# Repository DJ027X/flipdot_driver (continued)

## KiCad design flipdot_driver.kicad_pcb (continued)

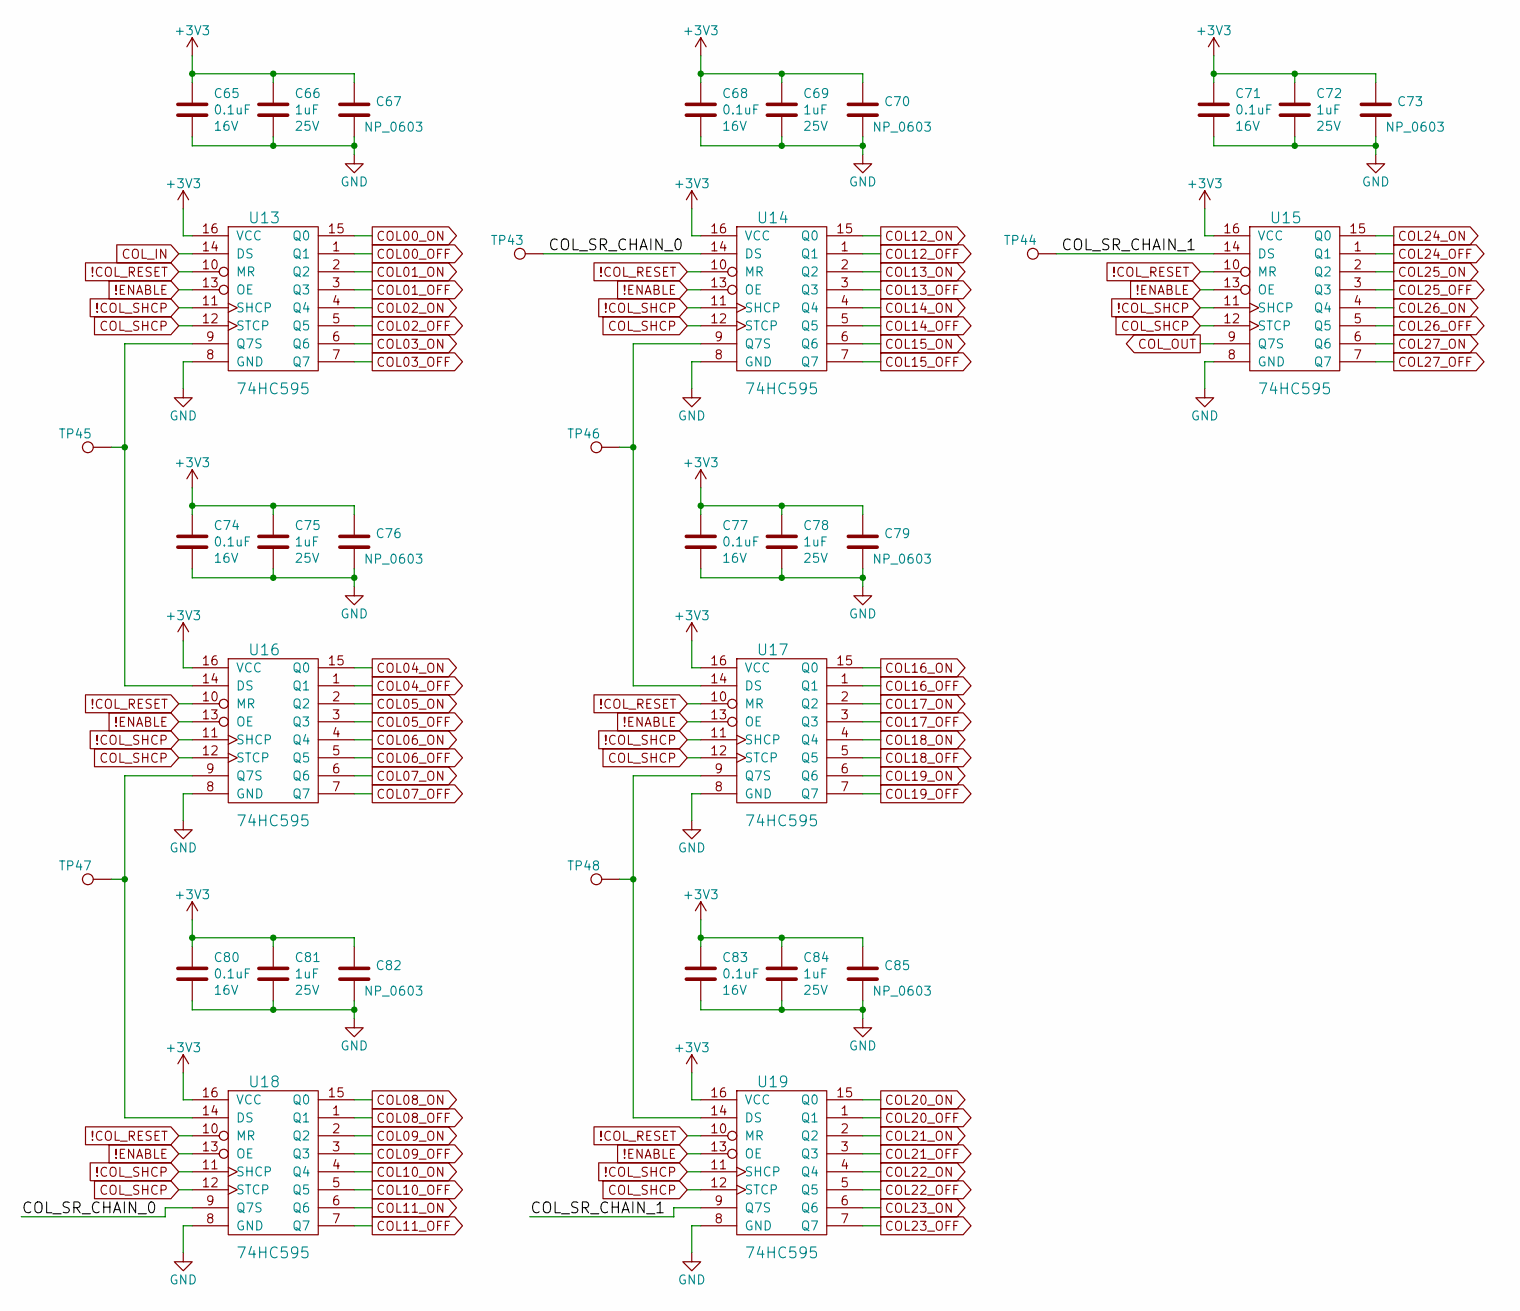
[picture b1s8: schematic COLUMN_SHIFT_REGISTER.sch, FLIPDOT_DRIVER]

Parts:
C65, C68, C71, C74, C77, C80, C83: CL10B104KO8NNNC; C_0603_1608Metric; Rating 16V
C66, C69, C72, C75, C78, C81, C84: CL10B105KA8NNNC; C_0603_1608Metric; Rating 25V
C67, C70, C73, C76, C79, C82, C85: NP_0603; C_0603_1608Metric
TP43, TP44, TP45, TP46, TP47, TP48: TestPoint; TestPoint_THTPad_D1.0mm_Drill0.5mm
U13, U14, U15, U16, U17, U18, U19: 74HC595; SOIC-16_3.9x9.9mm_P1.27mm

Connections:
!COL_RESET: U13.10 (MR), U14.10 (MR), U15.10 (MR), U16.10 (MR), U17.10 (MR), U18.10 (MR), U19.10 (MR); also elsewhere on the board
!COL_SHCP: U13.11 (SHCP), U14.11 (SHCP), U15.11 (SHCP), U16.11 (SHCP), U17.11 (SHCP), U18.11 (SHCP), U19.11 (SHCP); also elsewhere on the board
!ENABLE: U13.13 (OE), U14.13 (OE), U15.13 (OE), U16.13 (OE), U17.13 (OE), U18.13 (OE), U19.13 (OE); also elsewhere on the board
+3V3: C65.1, C66.1, C67.1, C68.1, C69.1, C70.1, C71.1, C72.1, C73.1, C74.1, C75.1, C76.1, C77.1, C78.1, C79.1, C80.1, C81.1, C82.1, C83.1, C84.1, C85.1, U13.16 (VCC), U14.16 (VCC), U15.16 (VCC), U16.16 (VCC), U17.16 (VCC), U18.16 (VCC), U19.16 (VCC); also elsewhere on the board
/COLUMN_SHIFT_REGISTER/COL_SR_CHAIN_0: TP43.1, U14.14 (DS), U18.9 (Q7S)
/COLUMN_SHIFT_REGISTER/COL_SR_CHAIN_1: TP44.1, U15.14 (DS), U19.9 (Q7S)
COL00_OFF: U13.1 (Q1); also elsewhere on the board
COL00_ON: U13.15 (Q0); also elsewhere on the board
COL01_OFF: U13.3 (Q3); also elsewhere on the board
COL01_ON: U13.2 (Q2); also elsewhere on the board
COL02_OFF: U13.5 (Q5); also elsewhere on the board
COL02_ON: U13.4 (Q4); also elsewhere on the board
COL03_OFF: U13.7 (Q7); also elsewhere on the board
COL03_ON: U13.6 (Q6); also elsewhere on the board
COL04_OFF: U16.1 (Q1); also elsewhere on the board
COL04_ON: U16.15 (Q0); also elsewhere on the board
COL05_OFF: U16.3 (Q3); also elsewhere on the board
COL05_ON: U16.2 (Q2); also elsewhere on the board
COL06_OFF: U16.5 (Q5); also elsewhere on the board
COL06_ON: U16.4 (Q4); also elsewhere on the board
COL07_OFF: U16.7 (Q7); also elsewhere on the board
COL07_ON: U16.6 (Q6); also elsewhere on the board
COL08_OFF: U18.1 (Q1); also elsewhere on the board
COL08_ON: U18.15 (Q0); also elsewhere on the board
COL09_OFF: U18.3 (Q3); also elsewhere on the board
COL09_ON: U18.2 (Q2); also elsewhere on the board
COL10_OFF: U18.5 (Q5); also elsewhere on the board
COL10_ON: U18.4 (Q4); also elsewhere on the board
COL11_OFF: U18.7 (Q7); also elsewhere on the board
COL11_ON: U18.6 (Q6); also elsewhere on the board
COL12_OFF: U14.1 (Q1); also elsewhere on the board
COL12_ON: U14.15 (Q0); also elsewhere on the board
COL13_OFF: U14.3 (Q3); also elsewhere on the board
COL13_ON: U14.2 (Q2); also elsewhere on the board
COL14_OFF: U14.5 (Q5); also elsewhere on the board
COL14_ON: U14.4 (Q4); also elsewhere on the board
COL15_OFF: U14.7 (Q7); also elsewhere on the board
COL15_ON: U14.6 (Q6); also elsewhere on the board
COL16_OFF: U17.1 (Q1); also elsewhere on the board
COL16_ON: U17.15 (Q0); also elsewhere on the board
COL17_OFF: U17.3 (Q3); also elsewhere on the board
COL17_ON: U17.2 (Q2); also elsewhere on the board
COL18_OFF: U17.5 (Q5); also elsewhere on the board
COL18_ON: U17.4 (Q4); also elsewhere on the board
COL19_OFF: U17.7 (Q7); also elsewhere on the board
COL19_ON: U17.6 (Q6); also elsewhere on the board
COL20_OFF: U19.1 (Q1); also elsewhere on the board
COL20_ON: U19.15 (Q0); also elsewhere on the board
COL21_OFF: U19.3 (Q3); also elsewhere on the board
COL21_ON: U19.2 (Q2); also elsewhere on the board
COL22_OFF: U19.5 (Q5); also elsewhere on the board
COL22_ON: U19.4 (Q4); also elsewhere on the board
COL23_OFF: U19.7 (Q7); also elsewhere on the board
COL23_ON: U19.6 (Q6); also elsewhere on the board
COL24_OFF: U15.1 (Q1); also elsewhere on the board
COL24_ON: U15.15 (Q0); also elsewhere on the board
COL25_OFF: U15.3 (Q3); also elsewhere on the board
COL25_ON: U15.2 (Q2); also elsewhere on the board
COL26_OFF: U15.5 (Q5); also elsewhere on the board
COL26_ON: U15.4 (Q4); also elsewhere on the board
COL27_OFF: U15.7 (Q7); also elsewhere on the board
COL27_ON: U15.6 (Q6); also elsewhere on the board
COL_IN: U13.14 (DS); also elsewhere on the board
COL_OUT: U15.9 (Q7S); also elsewhere on the board
COL_SHCP: U13.12 (STCP), U14.12 (STCP), U15.12 (STCP), U16.12 (STCP), U17.12 (STCP), U18.12 (STCP), U19.12 (STCP); also elsewhere on the board
GND: C65.2, C66.2, C67.2, C68.2, C69.2, C70.2, C71.2, C72.2, C73.2, C74.2, C75.2, C76.2, C77.2, C78.2, C79.2, C80.2, C81.2, C82.2, C83.2, C84.2, C85.2, U13.8 (GND), U14.8 (GND), U15.8 (GND), U16.8 (GND), U17.8 (GND), U18.8 (GND), U19.8 (GND); also elsewhere on the board
unnamed: TP45.1, U13.9 (Q7S), U16.14 (DS)
unnamed: TP46.1, U14.9 (Q7S), U17.14 (DS)
unnamed: TP47.1, U16.9 (Q7S), U18.14 (DS)
unnamed: TP48.1, U17.9 (Q7S), U19.14 (DS)

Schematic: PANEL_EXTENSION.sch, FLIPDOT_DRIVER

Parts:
C86, C87: CL10B104KO8NNNC; C_0603_1608Metric; Rating 16V
J10: Conn_01x08_Male; PinHeader_1x08_P2.54mm_Horizontal
R89, R90, R91, R92: CRG0603F4K7; R_0603_1608Metric; TOLERANCE 5%
TP49, TP50, TP51, TP52, TP53, TP54, TP55, TP56, TP57, TP58, TP59, TP60: TestPoint; TestPoint_THTPad_D1.0mm_Drill0.5mm
U20, U22: SGM3157YC6; SOT-363_SC-70-6
U21, U23: CM1293A-04SO; SOT-457

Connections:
!COL_RESET: J10.3, TP58.1, U23.3 (CH2); also elsewhere on the board
!ENABLE: J10.2, TP59.1, U23.4 (CH3); also elsewhere on the board
+3V3: C86.1, C87.1, U20.5 (VCC), U21.5 (V+), U22.5 (VCC), U23.5 (V+); also elsewhere on the board
/PANEL_EXTENSION/COL_DATA: J10.5, R91.1, TP56.1, U21.6 (CH4), U22.4 (COM)
/PANEL_EXTENSION/ROW_DATA: J10.8, R89.1, TP53.1, U20.4 (COM), U21.1 (CH1)
COL_IN: TP52.1, U22.3 (N_OP); also elsewhere on the board
COL_MODE_SEL: R92.1, U22.6 (IN); also elsewhere on the board
COL_OUT: TP51.1, U22.1 (N_CL); also elsewhere on the board
COL_SHCP: J10.4, TP57.1, U23.1 (CH1); also elsewhere on the board
GND: C86.2, C87.2, J10.1, R89.2, R90.2, R91.2, R92.2, TP60.1, U20.2 (GND), U21.2 (V-), U22.2 (GND), U23.2 (V-), U23.6 (CH4); also elsewhere on the board
ROW_IN: TP50.1, U20.3 (N_OP); also elsewhere on the board
ROW_MODE_SEL: R90.1, U20.6 (IN); also elsewhere on the board
ROW_ON: J10.6, TP55.1, U21.4 (CH3); also elsewhere on the board
ROW_OUT: TP49.1, U20.1 (N_CL); also elsewhere on the board
ROW_SHCP: J10.7, TP54.1, U21.3 (CH2); also elsewhere on the board

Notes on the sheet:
CONN_GND

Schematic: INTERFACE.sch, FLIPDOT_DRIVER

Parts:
J11: 3x32_1&3_loaded_2.5mm_0.1in_female_header; 32x3_POP_1_3
Q15: DMG6602; TSOT-23-6
R93: CRG0603F4K7; R_0603_1608Metric; TOLERANCE 5%
TP61, TP62: TestPoint; TestPoint_THTPad_D1.0mm_Drill0.5mm

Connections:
+24V: J11.3, J11.4; also elsewhere on the board
COL00: J11.37; also elsewhere on the board
COL01: J11.38; also elsewhere on the board
COL02: J11.39; also elsewhere on the board
COL03: J11.40; also elsewhere on the board
COL04: J11.41; also elsewhere on the board
COL05: J11.42; also elsewhere on the board
COL06: J11.43; also elsewhere on the board
COL07: J11.44; also elsewhere on the board
COL08: J11.45; also elsewhere on the board
COL09: J11.46; also elsewhere on the board
COL10: J11.47; also elsewhere on the board
COL11: J11.48; also elsewhere on the board
COL12: J11.49; also elsewhere on the board
COL13: J11.50; also elsewhere on the board
COL14: J11.51; also elsewhere on the board
COL15: J11.52; also elsewhere on the board
COL16: J11.53; also elsewhere on the board
COL17: J11.54; also elsewhere on the board
COL18: J11.55; also elsewhere on the board
COL19: J11.56; also elsewhere on the board
COL20: J11.57; also elsewhere on the board
COL21: J11.58; also elsewhere on the board
COL22: J11.59; also elsewhere on the board
COL23: J11.60; also elsewhere on the board
COL24: J11.61; also elsewhere on the board
COL25: J11.62; also elsewhere on the board
COL26: J11.63; also elsewhere on the board
COL27: J11.64; also elsewhere on the board
GND: Q15.5 (S), R93.2; also elsewhere on the board
LED_PWM: Q15.1 (G), R93.1, TP62.1; also elsewhere on the board
unnamed: J11.1, J11.2, Q15.6 (D), TP61.1
ROW00N: J11.36; also elsewhere on the board
ROW00P: J11.35; also elsewhere on the board
ROW01N: J11.6; also elsewhere on the board
ROW01P: J11.5; also elsewhere on the board
ROW02N: J11.34; also elsewhere on the board
ROW02P: J11.33; also elsewhere on the board
ROW03N: J11.8; also elsewhere on the board
ROW03P: J11.7; also elsewhere on the board
ROW04N: J11.32; also elsewhere on the board
ROW04P: J11.31; also elsewhere on the board
ROW05N: J11.10; also elsewhere on the board
ROW05P: J11.9; also elsewhere on the board
ROW06N: J11.30; also elsewhere on the board
ROW06P: J11.29; also elsewhere on the board
ROW07N: J11.12; also elsewhere on the board
ROW07P: J11.11; also elsewhere on the board
ROW08N: J11.28; also elsewhere on the board
ROW08P: J11.27; also elsewhere on the board
ROW09N: J11.14; also elsewhere on the board
ROW09P: J11.13; also elsewhere on the board
ROW10N: J11.26; also elsewhere on the board
ROW10P: J11.25; also elsewhere on the board
ROW11N: J11.16; also elsewhere on the board
ROW11P: J11.15; also elsewhere on the board
ROW12N: J11.24; also elsewhere on the board
ROW12P: J11.23; also elsewhere on the board
ROW13N: J11.18; also elsewhere on the board
ROW13P: J11.17; also elsewhere on the board
ROW14N: J11.22; also elsewhere on the board
ROW14P: J11.21; also elsewhere on the board
ROW15N: J11.20; also elsewhere on the board
ROW15P: J11.19; also elsewhere on the board

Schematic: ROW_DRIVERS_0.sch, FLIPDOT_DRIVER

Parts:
D18, D19, D20, D21, D22, D23, D24, D25: MMBZ5243BLT1G; SOT-23; Rating 13V
Q16, Q17, Q20, Q21: DMG6602; TSOT-23-6
Q18, Q19, Q22, Q23: SSM3K35AMFV; SOT-723
R94, R95, R96, R97, R98, R99, R100, R101, R102, R103, R104, R105: CRG0603F4K7; R_0603_1608Metric; TOLERANCE 5%
TP63, TP64, TP66, TP68, TP70, TP72, TP74: TestPoint; TestPoint_THTPad_D1.0mm_Drill0.5mm

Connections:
+12V: D18.1 (K), D19.1 (K), D22.1 (K), D23.1 (K), Q16.2 (S), Q17.2 (S), Q20.2 (S), Q21.2 (S), R94.1, R95.1, R100.1, R101.1, TP63.1; also elsewhere on the board
GND: D20.2 (A), D21.2 (A), D24.2 (A), D25.2 (A), Q16.5 (S), Q17.5 (S), Q18.2 (S), Q19.2 (S), Q20.5 (S), Q21.5 (S), Q22.2 (S), Q23.2 (S), R96.2, R97.2, R98.2, R99.2, R102.2, R103.2, R104.2, R105.2, TP70.1; also elsewhere on the board
unnamed: Q16.3 (G), Q18.3 (D), R94.2, TP64.1
unnamed: Q17.3 (G), Q19.3 (D), R95.2
unnamed: Q20.3 (G), Q22.3 (D), R100.2
unnamed: Q21.3 (G), Q23.3 (D), R101.2
ROW00N: D20.1 (K), Q16.6 (D), TP72.1; also elsewhere on the board
ROW00P: D18.2 (A), Q16.4 (D), TP68.1; also elsewhere on the board
ROW00_OFF: Q16.1 (G), R98.1, TP74.1; also elsewhere on the board
ROW00_ON: Q18.1 (G), R96.1, TP66.1; also elsewhere on the board
ROW01N: D21.1 (K), Q17.6 (D); also elsewhere on the board
ROW01P: D19.2 (A), Q17.4 (D); also elsewhere on the board
ROW01_OFF: Q17.1 (G), R99.1; also elsewhere on the board
ROW01_ON: Q19.1 (G), R97.1; also elsewhere on the board
ROW02N: D24.1 (K), Q20.6 (D); also elsewhere on the board
ROW02P: D22.2 (A), Q20.4 (D); also elsewhere on the board
ROW02_OFF: Q20.1 (G), R104.1; also elsewhere on the board
ROW02_ON: Q22.1 (G), R102.1; also elsewhere on the board
ROW03N: D25.1 (K), Q21.6 (D); also elsewhere on the board
ROW03P: D23.2 (A), Q21.4 (D); also elsewhere on the board
ROW03_OFF: Q21.1 (G), R105.1; also elsewhere on the board
ROW03_ON: Q23.1 (G), R103.1; also elsewhere on the board

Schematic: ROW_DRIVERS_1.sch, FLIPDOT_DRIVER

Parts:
D26, D27, D28, D29, D30, D31, D32, D33: MMBZ5243BLT1G; SOT-23; Rating 13V
Q24, Q25, Q28, Q29: DMG6602; TSOT-23-6
Q26, Q27, Q30, Q31: SSM3K35AMFV; SOT-723
R106, R107, R108, R109, R110, R111, R112, R113, R114, R115, R116, R117: CRG0603F4K7; R_0603_1608Metric; TOLERANCE 5%

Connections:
+12V: D26.1 (K), D27.1 (K), D30.1 (K), D31.1 (K), Q24.2 (S), Q25.2 (S), Q28.2 (S), Q29.2 (S), R106.1, R107.1, R112.1, R113.1; also elsewhere on the board
GND: D28.2 (A), D29.2 (A), D32.2 (A), D33.2 (A), Q24.5 (S), Q25.5 (S), Q26.2 (S), Q27.2 (S), Q28.5 (S), Q29.5 (S), Q30.2 (S), Q31.2 (S), R108.2, R109.2, R110.2, R111.2, R114.2, R115.2, R116.2, R117.2; also elsewhere on the board
unnamed: Q24.3 (G), Q26.3 (D), R106.2
unnamed: Q25.3 (G), Q27.3 (D), R107.2
unnamed: Q28.3 (G), Q30.3 (D), R112.2
unnamed: Q29.3 (G), Q31.3 (D), R113.2
ROW04N: D28.1 (K), Q24.6 (D); also elsewhere on the board
ROW04P: D26.2 (A), Q24.4 (D); also elsewhere on the board
ROW04_OFF: Q24.1 (G), R110.1; also elsewhere on the board
ROW04_ON: Q26.1 (G), R108.1; also elsewhere on the board
ROW05N: D29.1 (K), Q25.6 (D); also elsewhere on the board
ROW05P: D27.2 (A), Q25.4 (D); also elsewhere on the board
ROW05_OFF: Q25.1 (G), R111.1; also elsewhere on the board
ROW05_ON: Q27.1 (G), R109.1; also elsewhere on the board
ROW06N: D32.1 (K), Q28.6 (D); also elsewhere on the board
ROW06P: D30.2 (A), Q28.4 (D); also elsewhere on the board
ROW06_OFF: Q28.1 (G), R116.1; also elsewhere on the board
ROW06_ON: Q30.1 (G), R114.1; also elsewhere on the board
ROW07N: D33.1 (K), Q29.6 (D); also elsewhere on the board
ROW07P: D31.2 (A), Q29.4 (D); also elsewhere on the board
ROW07_OFF: Q29.1 (G), R117.1; also elsewhere on the board
ROW07_ON: Q31.1 (G), R115.1; also elsewhere on the board

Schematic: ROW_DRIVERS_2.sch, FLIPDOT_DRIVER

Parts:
D34, D35, D36, D37, D38, D39, D40, D41: MMBZ5243BLT1G; SOT-23; Rating 13V
Q32, Q33, Q36, Q37: DMG6602; TSOT-23-6
Q34, Q35, Q38, Q39: SSM3K35AMFV; SOT-723
R118, R119, R120, R121, R122, R123, R124, R125, R126, R127, R128, R129: CRG0603F4K7; R_0603_1608Metric; TOLERANCE 5%

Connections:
+12V: D34.1 (K), D35.1 (K), D38.1 (K), D39.1 (K), Q32.2 (S), Q33.2 (S), Q36.2 (S), Q37.2 (S), R118.1, R119.1, R124.1, R125.1; also elsewhere on the board
GND: D36.2 (A), D37.2 (A), D40.2 (A), D41.2 (A), Q32.5 (S), Q33.5 (S), Q34.2 (S), Q35.2 (S), Q36.5 (S), Q37.5 (S), Q38.2 (S), Q39.2 (S), R120.2, R121.2, R122.2, R123.2, R126.2, R127.2, R128.2, R129.2; also elsewhere on the board
unnamed: Q32.3 (G), Q34.3 (D), R118.2
unnamed: Q33.3 (G), Q35.3 (D), R119.2
unnamed: Q36.3 (G), Q38.3 (D), R124.2
unnamed: Q37.3 (G), Q39.3 (D), R125.2
ROW08N: D36.1 (K), Q32.6 (D); also elsewhere on the board
ROW08P: D34.2 (A), Q32.4 (D); also elsewhere on the board
ROW08_OFF: Q32.1 (G), R122.1; also elsewhere on the board
ROW08_ON: Q34.1 (G), R120.1; also elsewhere on the board
ROW09N: D37.1 (K), Q33.6 (D); also elsewhere on the board
ROW09P: D35.2 (A), Q33.4 (D); also elsewhere on the board
ROW09_OFF: Q33.1 (G), R123.1; also elsewhere on the board
ROW09_ON: Q35.1 (G), R121.1; also elsewhere on the board
ROW10N: D40.1 (K), Q36.6 (D); also elsewhere on the board
ROW10P: D38.2 (A), Q36.4 (D); also elsewhere on the board
ROW10_OFF: Q36.1 (G), R128.1; also elsewhere on the board
ROW10_ON: Q38.1 (G), R126.1; also elsewhere on the board
ROW11N: D41.1 (K), Q37.6 (D); also elsewhere on the board
ROW11P: D39.2 (A), Q37.4 (D); also elsewhere on the board
ROW11_OFF: Q37.1 (G), R129.1; also elsewhere on the board
ROW11_ON: Q39.1 (G), R127.1; also elsewhere on the board

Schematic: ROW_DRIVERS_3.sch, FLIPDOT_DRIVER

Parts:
D42, D43, D44, D45, D46, D47, D48, D49: MMBZ5243BLT1G; SOT-23; Rating 13V
Q40, Q41, Q44, Q45: DMG6602; TSOT-23-6
Q42, Q43, Q46, Q47: SSM3K35AMFV; SOT-723
R130, R131, R132, R133, R134, R135, R136, R137, R138, R139, R140, R141: CRG0603F4K7; R_0603_1608Metric; TOLERANCE 5%

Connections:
+12V: D42.1 (K), D43.1 (K), D46.1 (K), D47.1 (K), Q40.2 (S), Q41.2 (S), Q44.2 (S), Q45.2 (S), R130.1, R131.1, R136.1, R137.1; also elsewhere on the board
GND: D44.2 (A), D45.2 (A), D48.2 (A), D49.2 (A), Q40.5 (S), Q41.5 (S), Q42.2 (S), Q43.2 (S), Q44.5 (S), Q45.5 (S), Q46.2 (S), Q47.2 (S), R132.2, R133.2, R134.2, R135.2, R138.2, R139.2, R140.2, R141.2; also elsewhere on the board
unnamed: Q40.3 (G), Q42.3 (D), R130.2
unnamed: Q41.3 (G), Q43.3 (D), R131.2
unnamed: Q44.3 (G), Q46.3 (D), R136.2
unnamed: Q45.3 (G), Q47.3 (D), R137.2
ROW12N: D44.1 (K), Q40.6 (D); also elsewhere on the board
ROW12P: D42.2 (A), Q40.4 (D); also elsewhere on the board
ROW12_OFF: Q40.1 (G), R134.1; also elsewhere on the board
ROW12_ON: Q42.1 (G), R132.1; also elsewhere on the board
ROW13N: D45.1 (K), Q41.6 (D); also elsewhere on the board
ROW13P: D43.2 (A), Q41.4 (D); also elsewhere on the board
ROW13_OFF: Q41.1 (G), R135.1; also elsewhere on the board
ROW13_ON: Q43.1 (G), R133.1; also elsewhere on the board
ROW14N: D48.1 (K), Q44.6 (D); also elsewhere on the board
ROW14P: D46.2 (A), Q44.4 (D); also elsewhere on the board
ROW14_OFF: Q44.1 (G), R140.1; also elsewhere on the board
ROW14_ON: Q46.1 (G), R138.1; also elsewhere on the board
ROW15N: D49.1 (K), Q45.6 (D); also elsewhere on the board
ROW15P: D47.2 (A), Q45.4 (D); also elsewhere on the board
ROW15_OFF: Q45.1 (G), R141.1; also elsewhere on the board
ROW15_ON: Q47.1 (G), R139.1; also elsewhere on the board

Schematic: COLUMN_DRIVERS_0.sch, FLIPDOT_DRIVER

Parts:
Q48, Q49, Q50, Q57, Q58, Q59: DMG6602; TSOT-23-6
Q51, Q52, Q53, Q54, Q55, Q56, Q60, Q61, Q62, Q63, Q64, Q65: SSM3K35AMFV; SOT-723
R142, R143, R144, R145, R146, R147, R148, R149, R150, R151, R152, R153, R154, R155, R156, R157, R158, R159, R160, R161, R162, R163, R164, R165: CRG0603F4K7; R_0603_1608Metric; TOLERANCE 5%
TP78, TP80, TP82, TP83, TP84, TP88, TP90: TestPoint; TestPoint_THTPad_D1.0mm_Drill0.5mm

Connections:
+12V: Q48.2 (S), Q49.2 (S), Q50.2 (S), Q57.2 (S), Q58.2 (S), Q59.2 (S), R142.1, R143.1, R144.1, R154.1, R155.1, R156.1, TP78.1; also elsewhere on the board
COL00: Q48.4 (D), Q48.6 (D), TP84.1; also elsewhere on the board
COL00_OFF: R145.2, R149.1, TP82.1; also elsewhere on the board
COL00_ON: Q51.1 (G), Q54.1 (G), R148.1, TP83.1; also elsewhere on the board
COL01: Q49.4 (D), Q49.6 (D); also elsewhere on the board
COL01_OFF: R146.2, R151.1; also elsewhere on the board
COL01_ON: Q52.1 (G), Q55.1 (G), R150.1; also elsewhere on the board
COL02: Q50.4 (D), Q50.6 (D); also elsewhere on the board
COL02_OFF: R147.2, R153.1; also elsewhere on the board
COL02_ON: Q53.1 (G), Q56.1 (G), R152.1; also elsewhere on the board
COL03: Q57.4 (D), Q57.6 (D); also elsewhere on the board
COL03_OFF: R157.2, R161.1; also elsewhere on the board
COL03_ON: Q60.1 (G), Q63.1 (G), R160.1; also elsewhere on the board
COL04: Q58.4 (D), Q58.6 (D); also elsewhere on the board
COL04_OFF: R158.2, R163.1; also elsewhere on the board
COL04_ON: Q61.1 (G), Q64.1 (G), R162.1; also elsewhere on the board
COL05: Q59.4 (D), Q59.6 (D); also elsewhere on the board
COL05_OFF: R159.2, R165.1; also elsewhere on the board
COL05_ON: Q62.1 (G), Q65.1 (G), R164.1; also elsewhere on the board
GND: Q48.5 (S), Q49.5 (S), Q50.5 (S), Q51.2 (S), Q52.2 (S), Q53.2 (S), Q54.2 (S), Q55.2 (S), Q56.2 (S), Q57.5 (S), Q58.5 (S), Q59.5 (S), Q60.2 (S), Q61.2 (S), Q62.2 (S), Q63.2 (S), Q64.2 (S), Q65.2 (S), R148.2, R149.2, R150.2, R151.2, R152.2, R153.2, R160.2, R161.2, R162.2, R163.2, R164.2, R165.2, TP90.1; also elsewhere on the board
unnamed: Q48.1 (G), Q54.3 (D), R145.1, TP88.1
unnamed: Q48.3 (G), Q51.3 (D), R142.2, TP80.1
unnamed: Q49.1 (G), Q55.3 (D), R146.1
unnamed: Q49.3 (G), Q52.3 (D), R143.2
unnamed: Q50.1 (G), Q56.3 (D), R147.1
unnamed: Q50.3 (G), Q53.3 (D), R144.2
unnamed: Q57.1 (G), Q63.3 (D), R157.1
unnamed: Q57.3 (G), Q60.3 (D), R154.2
unnamed: Q58.1 (G), Q64.3 (D), R158.1
unnamed: Q58.3 (G), Q61.3 (D), R155.2
unnamed: Q59.1 (G), Q65.3 (D), R159.1
unnamed: Q59.3 (G), Q62.3 (D), R156.2

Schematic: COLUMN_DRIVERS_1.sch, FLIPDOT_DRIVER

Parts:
Q66, Q67, Q68, Q75, Q76, Q77: DMG6602; TSOT-23-6
Q69, Q70, Q71, Q72, Q73, Q74, Q78, Q79, Q80, Q81, Q82, Q83: SSM3K35AMFV; SOT-723
R166, R167, R168, R169, R170, R171, R172, R173, R174, R175, R176, R177, R178, R179, R180, R181, R182, R183, R184, R185, R186, R187, R188, R189: CRG0603F4K7; R_0603_1608Metric; TOLERANCE 5%

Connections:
+12V: Q66.2 (S), Q67.2 (S), Q68.2 (S), Q75.2 (S), Q76.2 (S), Q77.2 (S), R166.1, R167.1, R168.1, R178.1, R179.1, R180.1; also elsewhere on the board
COL06: Q66.4 (D), Q66.6 (D); also elsewhere on the board
COL06_OFF: R169.2, R173.1; also elsewhere on the board
COL06_ON: Q69.1 (G), Q72.1 (G), R172.1; also elsewhere on the board
COL07: Q67.4 (D), Q67.6 (D); also elsewhere on the board
COL07_OFF: R170.2, R175.1; also elsewhere on the board
COL07_ON: Q70.1 (G), Q73.1 (G), R174.1; also elsewhere on the board
COL08: Q68.4 (D), Q68.6 (D); also elsewhere on the board
COL08_OFF: R171.2, R177.1; also elsewhere on the board
COL08_ON: Q71.1 (G), Q74.1 (G), R176.1; also elsewhere on the board
COL09: Q75.4 (D), Q75.6 (D); also elsewhere on the board
COL09_OFF: R181.2, R185.1; also elsewhere on the board
COL09_ON: Q78.1 (G), Q81.1 (G), R184.1; also elsewhere on the board
COL10: Q76.4 (D), Q76.6 (D); also elsewhere on the board
COL10_OFF: R182.2, R187.1; also elsewhere on the board
COL10_ON: Q79.1 (G), Q82.1 (G), R186.1; also elsewhere on the board
COL11: Q77.4 (D), Q77.6 (D); also elsewhere on the board
COL11_OFF: R183.2, R189.1; also elsewhere on the board
COL11_ON: Q80.1 (G), Q83.1 (G), R188.1; also elsewhere on the board
GND: Q66.5 (S), Q67.5 (S), Q68.5 (S), Q69.2 (S), Q70.2 (S), Q71.2 (S), Q72.2 (S), Q73.2 (S), Q74.2 (S), Q75.5 (S), Q76.5 (S), Q77.5 (S), Q78.2 (S), Q79.2 (S), Q80.2 (S), Q81.2 (S), Q82.2 (S), Q83.2 (S), R172.2, R173.2, R174.2, R175.2, R176.2, R177.2, R184.2, R185.2, R186.2, R187.2, R188.2, R189.2; also elsewhere on the board
unnamed: Q66.1 (G), Q72.3 (D), R169.1
unnamed: Q66.3 (G), Q69.3 (D), R166.2
unnamed: Q67.1 (G), Q73.3 (D), R170.1
unnamed: Q67.3 (G), Q70.3 (D), R167.2
unnamed: Q68.1 (G), Q74.3 (D), R171.1
unnamed: Q68.3 (G), Q71.3 (D), R168.2
unnamed: Q75.1 (G), Q81.3 (D), R181.1
unnamed: Q75.3 (G), Q78.3 (D), R178.2
unnamed: Q76.1 (G), Q82.3 (D), R182.1
unnamed: Q76.3 (G), Q79.3 (D), R179.2
unnamed: Q77.1 (G), Q83.3 (D), R183.1
unnamed: Q77.3 (G), Q80.3 (D), R180.2

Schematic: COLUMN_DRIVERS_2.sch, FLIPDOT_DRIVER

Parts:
Q84, Q85, Q86, Q93, Q94, Q95: DMG6602; TSOT-23-6
Q87, Q88, Q89, Q90, Q91, Q92, Q96, Q97, Q98, Q99, Q100, Q101: SSM3K35AMFV; SOT-723
R190, R191, R192, R193, R194, R195, R196, R197, R198, R199, R200, R201, R202, R203, R204, R205, R206, R207, R208, R209, R210, R211, R212, R213: CRG0603F4K7; R_0603_1608Metric; TOLERANCE 5%

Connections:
+12V: Q84.2 (S), Q85.2 (S), Q86.2 (S), Q93.2 (S), Q94.2 (S), Q95.2 (S), R190.1, R191.1, R192.1, R202.1, R203.1, R204.1; also elsewhere on the board
COL12: Q84.4 (D), Q84.6 (D); also elsewhere on the board
COL12_OFF: R193.2, R197.1; also elsewhere on the board
COL12_ON: Q87.1 (G), Q90.1 (G), R196.1; also elsewhere on the board
COL13: Q85.4 (D), Q85.6 (D); also elsewhere on the board
COL13_OFF: R194.2, R199.1; also elsewhere on the board
COL13_ON: Q88.1 (G), Q91.1 (G), R198.1; also elsewhere on the board
COL14: Q86.4 (D), Q86.6 (D); also elsewhere on the board
COL14_OFF: R195.2, R201.1; also elsewhere on the board
COL14_ON: Q89.1 (G), Q92.1 (G), R200.1; also elsewhere on the board
COL15: Q93.4 (D), Q93.6 (D); also elsewhere on the board
COL15_OFF: R205.2, R209.1; also elsewhere on the board
COL15_ON: Q96.1 (G), Q99.1 (G), R208.1; also elsewhere on the board
COL16: Q94.4 (D), Q94.6 (D); also elsewhere on the board
COL16_OFF: R206.2, R211.1; also elsewhere on the board
COL16_ON: Q97.1 (G), Q100.1 (G), R210.1; also elsewhere on the board
COL17: Q95.4 (D), Q95.6 (D); also elsewhere on the board
COL17_OFF: R207.2, R213.1; also elsewhere on the board
COL17_ON: Q98.1 (G), Q101.1 (G), R212.1; also elsewhere on the board
GND: Q84.5 (S), Q85.5 (S), Q86.5 (S), Q87.2 (S), Q88.2 (S), Q89.2 (S), Q90.2 (S), Q91.2 (S), Q92.2 (S), Q93.5 (S), Q94.5 (S), Q95.5 (S), Q96.2 (S), Q97.2 (S), Q98.2 (S), Q99.2 (S), Q100.2 (S), Q101.2 (S), R196.2, R197.2, R198.2, R199.2, R200.2, R201.2, R208.2, R209.2, R210.2, R211.2, R212.2, R213.2; also elsewhere on the board
unnamed: Q84.1 (G), Q90.3 (D), R193.1
unnamed: Q84.3 (G), Q87.3 (D), R190.2
unnamed: Q85.1 (G), Q91.3 (D), R194.1
unnamed: Q85.3 (G), Q88.3 (D), R191.2
unnamed: Q86.1 (G), Q92.3 (D), R195.1
unnamed: Q86.3 (G), Q89.3 (D), R192.2
unnamed: Q93.1 (G), Q99.3 (D), R205.1
unnamed: Q93.3 (G), Q96.3 (D), R202.2
unnamed: Q94.3 (G), Q97.3 (D), R203.2
unnamed: Q95.3 (G), Q98.3 (D), R204.2
unnamed: Q94.1 (G), Q100.3 (D), R206.1
unnamed: Q95.1 (G), Q101.3 (D), R207.1

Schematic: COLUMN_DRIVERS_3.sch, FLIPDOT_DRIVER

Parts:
Q102, Q103, Q104, Q111, Q112, Q113: DMG6602; TSOT-23-6
Q105, Q106, Q107, Q108, Q109, Q110, Q114, Q115, Q116, Q117, Q118, Q119: SSM3K35AMFV; SOT-723
R214, R215, R216, R217, R218, R219, R220, R221, R222, R223, R224, R225, R226, R227, R228, R229, R230, R231, R232, R233, R234, R235, R236, R237: CRG0603F4K7; R_0603_1608Metric; TOLERANCE 5%

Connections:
+12V: Q102.2 (S), Q103.2 (S), Q104.2 (S), Q111.2 (S), Q112.2 (S), Q113.2 (S), R214.1, R215.1, R216.1, R226.1, R227.1, R228.1; also elsewhere on the board
COL18: Q102.4 (D), Q102.6 (D); also elsewhere on the board
COL18_OFF: R217.2, R221.1; also elsewhere on the board
COL18_ON: Q105.1 (G), Q108.1 (G), R220.1; also elsewhere on the board
COL19: Q103.4 (D), Q103.6 (D); also elsewhere on the board
COL19_OFF: R218.2, R223.1; also elsewhere on the board
COL19_ON: Q106.1 (G), Q109.1 (G), R222.1; also elsewhere on the board
COL20: Q104.4 (D), Q104.6 (D); also elsewhere on the board
COL20_OFF: R219.2, R225.1; also elsewhere on the board
COL20_ON: Q107.1 (G), Q110.1 (G), R224.1; also elsewhere on the board
COL21: Q111.4 (D), Q111.6 (D); also elsewhere on the board
COL21_OFF: R229.2, R233.1; also elsewhere on the board
COL21_ON: Q114.1 (G), Q117.1 (G), R232.1; also elsewhere on the board
COL22: Q112.4 (D), Q112.6 (D); also elsewhere on the board
COL22_OFF: R230.2, R235.1; also elsewhere on the board
COL22_ON: Q115.1 (G), Q118.1 (G), R234.1; also elsewhere on the board
COL23: Q113.4 (D), Q113.6 (D); also elsewhere on the board
COL23_OFF: R231.2, R237.1; also elsewhere on the board
COL23_ON: Q116.1 (G), Q119.1 (G), R236.1; also elsewhere on the board
GND: Q102.5 (S), Q103.5 (S), Q104.5 (S), Q105.2 (S), Q106.2 (S), Q107.2 (S), Q108.2 (S), Q109.2 (S), Q110.2 (S), Q111.5 (S), Q112.5 (S), Q113.5 (S), Q114.2 (S), Q115.2 (S), Q116.2 (S), Q117.2 (S), Q118.2 (S), Q119.2 (S), R220.2, R221.2, R222.2, R223.2, R224.2, R225.2, R232.2, R233.2, R234.2, R235.2, R236.2, R237.2; also elsewhere on the board
unnamed: Q102.1 (G), Q108.3 (D), R217.1
unnamed: Q102.3 (G), Q105.3 (D), R214.2
unnamed: Q103.1 (G), Q109.3 (D), R218.1
unnamed: Q103.3 (G), Q106.3 (D), R215.2
unnamed: Q104.1 (G), Q110.3 (D), R219.1
unnamed: Q104.3 (G), Q107.3 (D), R216.2
unnamed: Q111.1 (G), Q117.3 (D), R229.1
unnamed: Q111.3 (G), Q114.3 (D), R226.2
unnamed: Q112.1 (G), Q118.3 (D), R230.1
unnamed: Q112.3 (G), Q115.3 (D), R227.2
unnamed: Q113.1 (G), Q119.3 (D), R231.1
unnamed: Q113.3 (G), Q116.3 (D), R228.2

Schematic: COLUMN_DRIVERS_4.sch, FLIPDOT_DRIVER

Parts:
Q120, Q121, Q122, Q129: DMG6602; TSOT-23-6
Q123, Q124, Q125, Q126, Q127, Q128, Q130, Q131: SSM3K35AMFV; SOT-723
R238, R239, R240, R241, R242, R243, R244, R245, R246, R247, R248, R249, R250, R251, R252, R253: CRG0603F4K7; R_0603_1608Metric; TOLERANCE 5%

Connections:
+12V: Q120.2 (S), Q121.2 (S), Q122.2 (S), Q129.2 (S), R238.1, R239.1, R240.1, R250.1; also elsewhere on the board
COL24: Q120.4 (D), Q120.6 (D); also elsewhere on the board
COL24_OFF: R241.2, R245.1; also elsewhere on the board
COL24_ON: Q123.1 (G), Q126.1 (G), R244.1; also elsewhere on the board
COL25: Q121.4 (D), Q121.6 (D); also elsewhere on the board
COL25_OFF: R242.2, R247.1; also elsewhere on the board
COL25_ON: Q124.1 (G), Q127.1 (G), R246.1; also elsewhere on the board
COL26: Q122.4 (D), Q122.6 (D); also elsewhere on the board
COL26_OFF: R243.2, R249.1; also elsewhere on the board
COL26_ON: Q125.1 (G), Q128.1 (G), R248.1; also elsewhere on the board
COL27: Q129.4 (D), Q129.6 (D); also elsewhere on the board
COL27_OFF: R251.2, R253.1; also elsewhere on the board
COL27_ON: Q130.1 (G), Q131.1 (G), R252.1; also elsewhere on the board
GND: Q120.5 (S), Q121.5 (S), Q122.5 (S), Q123.2 (S), Q124.2 (S), Q125.2 (S), Q126.2 (S), Q127.2 (S), Q128.2 (S), Q129.5 (S), Q130.2 (S), Q131.2 (S), R244.2, R245.2, R246.2, R247.2, R248.2, R249.2, R252.2, R253.2; also elsewhere on the board
unnamed: Q120.1 (G), Q126.3 (D), R241.1
unnamed: Q120.3 (G), Q123.3 (D), R238.2
unnamed: Q121.1 (G), Q127.3 (D), R242.1
unnamed: Q121.3 (G), Q124.3 (D), R239.2
unnamed: Q122.1 (G), Q128.3 (D), R243.1
unnamed: Q122.3 (G), Q125.3 (D), R240.2
unnamed: Q129.1 (G), Q131.3 (D), R251.1
unnamed: Q129.3 (G), Q130.3 (D), R250.2

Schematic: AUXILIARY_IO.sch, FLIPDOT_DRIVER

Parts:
D11, D12: LED_GENERIC_0805; D_0805_2012Metric
J3: Conn_01x03_Male; PinHeader_1x03_P2.54mm_Horizontal
J4, J5, J6: PTH_1.5_mm; TestPoint_THTPad_D3.0mm_Drill1.5mm
Q4, Q5: SSM3K35AMFV; SOT-723
R20, R26, R36: ‎RMCF0603FT470R‎; R_0603_1608Metric; TOLERANCE 1%
R28, R35, R37: CRG0603F4K7; R_0603_1608Metric; TOLERANCE 5%
SW1, SW3, SW4: TACTILE_SWITCH_SMALL
U6: NP_CM1293A-04SO; SOT-457

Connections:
+3V3: R20.1, R26.1, R36.1, SW1.2, SW3.2, SW4.2, U6.4 (CH3), U6.5 (V+); also elsewhere on the board
GND: Q4.2 (S), Q5.2 (S), R28.2, R35.2, R37.2, U6.2 (V-); also elsewhere on the board
unnamed: D11.1 (K), Q4.3 (D)
unnamed: D12.1 (K), Q5.3 (D)

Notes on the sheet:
LABEL PINS ON SILKSCREEN
SILKSCREEN: POPULATE TVS DIODES AS APPROPRIATE FOR USE WITH GPIO PERIPHERALS

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
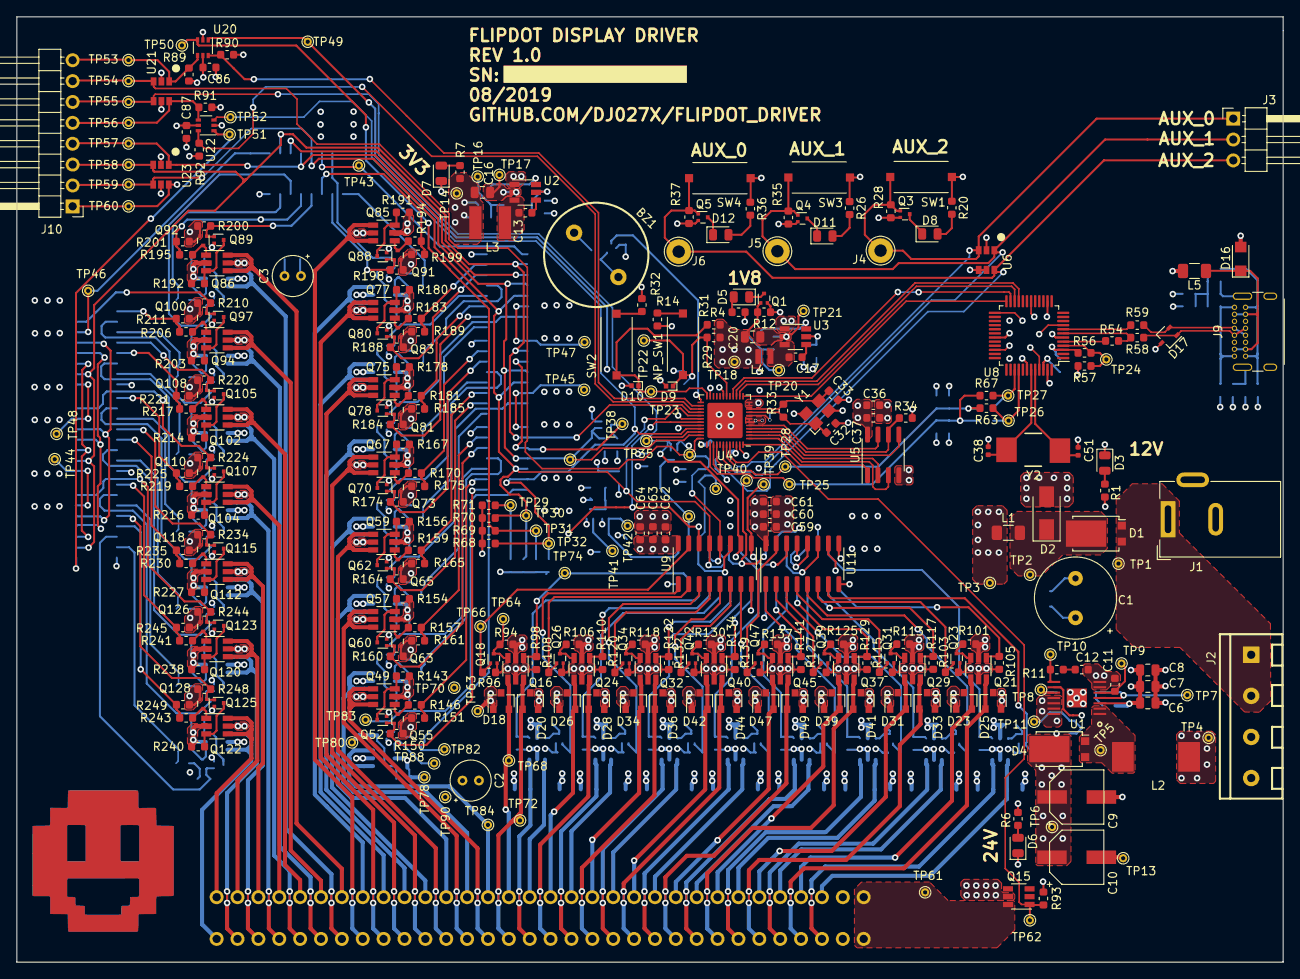
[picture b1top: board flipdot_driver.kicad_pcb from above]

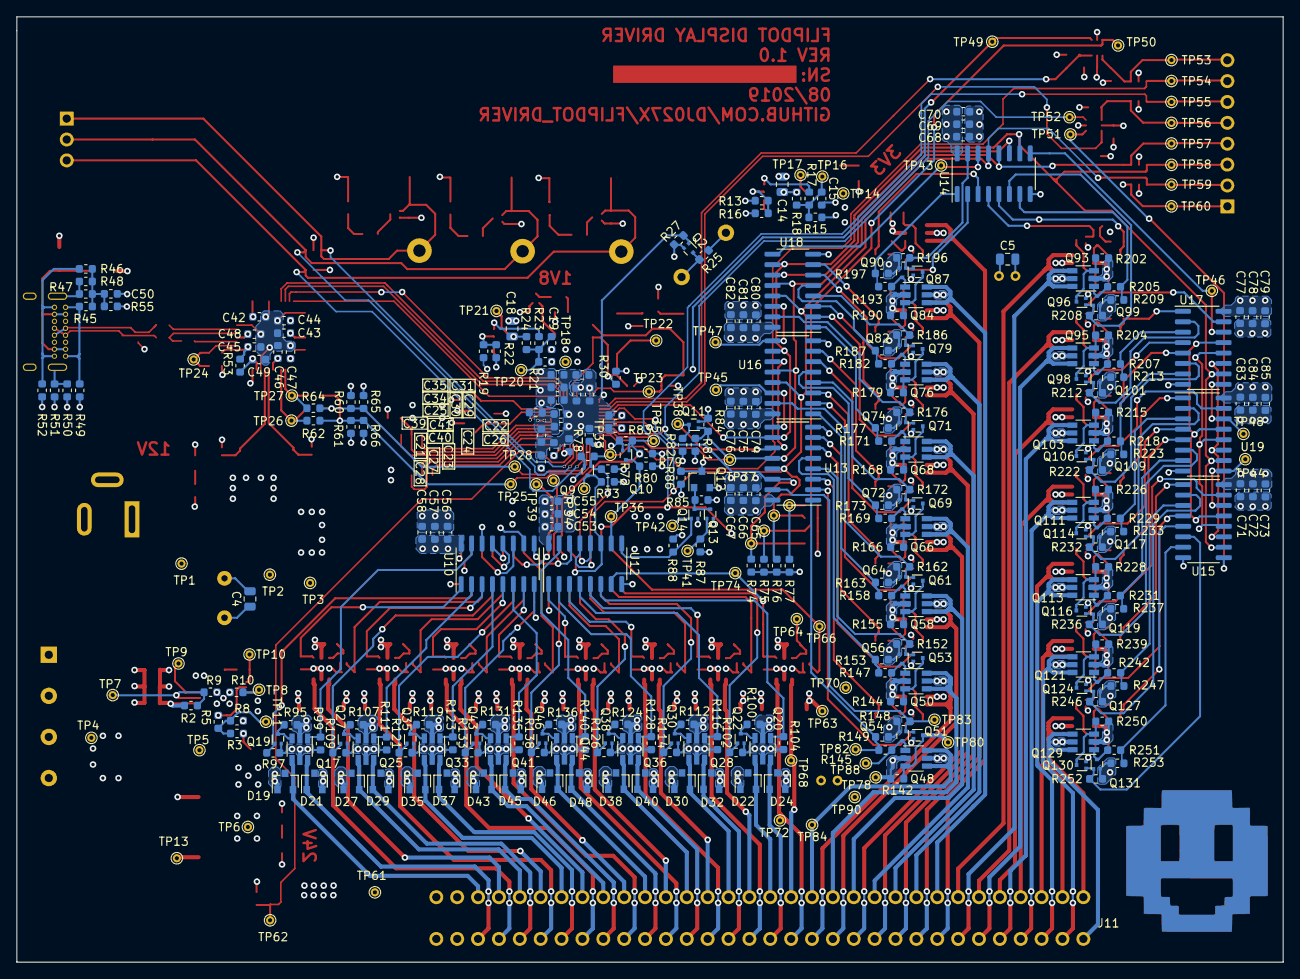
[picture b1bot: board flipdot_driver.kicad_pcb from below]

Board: 4 copper layers, 154.1 x 115.0 mm, 623 parts (300 on the bottom side), 327 nets.

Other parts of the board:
D8: LED_GENERIC_0805; D_0805_2012Metric
Q3: SSM3K35AMFV; SOT-723

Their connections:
GND: Q3.2; also elsewhere on the board
unnamed: D8.1, Q3.3

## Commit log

2017-12-10 added license
2017-12-11 replaced relatively large power MOSFETs with much more space-efficient N P pairs in a TSOT-23-6 package
2017-12-11 Updated progress section in README
2017-12-12 Added DC-DC converters to attain necessary voltage rails
2017-12-12 Sprinkled in some test points on the power circuitry
2017-12-23 Ignore this commit; shouldn't be any changes
2018-01-04 STARTED WORK ON CLOCK CIRCUITS FOR FE310-G000 AND FTD2232D CHIPS. ALSO DECIDED TO OPTIMIZE DIGITAL BOARD/BOARD INTERFACE TO REDUCE CABLE COST BY ADDING OPTOISOLATORS ON THE BOARD, GETTING RID OF INVE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
2018-01-05 cleaned up clock circuits and created a footprint for the crystals. Still considering wheter to propgate the JTAG chain through all connected boards
2018-05-18 Thank goodness for version control! Accidentally deleted the signal inverters at some point, but the initial commit still had them! Added those, beefed up circuit protection with reverse input diode,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
2018-05-21 Update README.txt
    Progress updates
2018-05-22 Changed bias resistors to more sane values and included my kicad library
2018-05-23 moar bugfixes
2018-05-23 bugfixes and added aux io
2018-07-01 Moved my cucstom components here, and made a bunch of changes to schematic
2018-07-19 Cleaned repo up some
2018-07-25 updated whole project from kicad 4 to 5
2018-09-06 removed the need for 5V0 rail. Have begun building my library up with actual components, so that the schematic links to specific part numbers instead of generic symbols
2018-09-07 continued assigning caps to actual parts
2019-05-27 Swapped discrete TVS with arrays. Swapped LED PWM PMOS (Q89)
2019-06-06 automated commit
2019-06-08 Fixed page order again, annotated schamatic, and plotted a PDF
